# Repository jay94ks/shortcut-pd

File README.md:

# Simple Shortcut Keypad.
 This has six keys that are customizable, and this designed for disabled peoples. I'm working with disabled brother. he's a survivor of car-crash in highway, I don't know details. A few days ago, I asked him how to press `Ctrl + Alt + Del` key combinations, he answered that "I've gave up to press these kind of key combinations, forever". I thought that, if there is a special keyboard to help him, he will never need to give up to press complex key combinations. this project is for that.
 of course, this is also for gamers and quick `NSFW`, haha!

## Boards
This project is consisted of two boards. one is a USB hub port and `RP2040` board and other one is keypad board. this two boards are connected through `FPC` cable. and fixed by steel bolt bars.

### Lower board

### Upper board

### Assembly diagram

## Firmware
Work in progress

## Configuration Tool
Work in progress

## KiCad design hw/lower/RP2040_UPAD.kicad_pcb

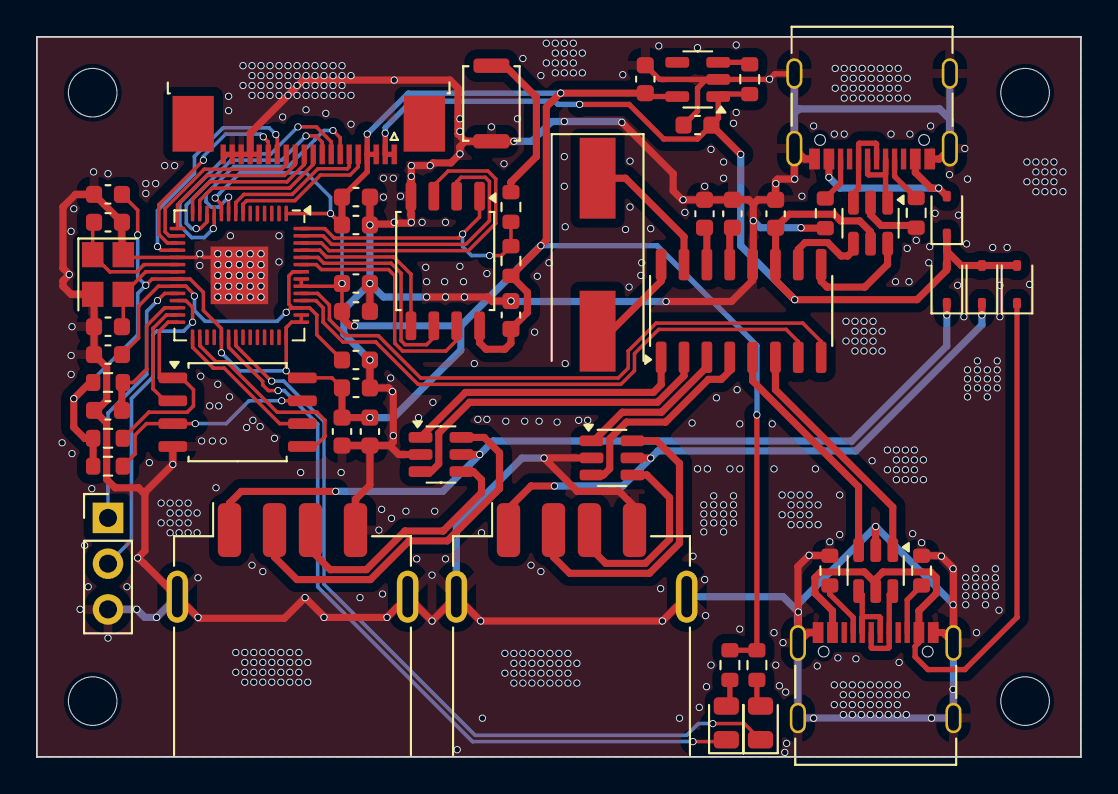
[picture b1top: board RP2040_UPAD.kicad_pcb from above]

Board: 2 copper layers, 58.0 x 40.0 mm, 59 parts (0 on the bottom side), 67 nets.

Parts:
C1, C8, C9, C10, C11, C13, C14, C15, C16: 100nF; C_0603_1608Metric
C2, C3: 30pF; C_0603_1608Metric
C5, C6, C7: 2.2uF; C_0603_1608Metric
C17, C18, C19, C20, C21: 10uF; C_0603_1608Metric
D1: LED/R; LED_0805_2012Metric
D2: LED/B; LED_0805_2012Metric
D3, D4, D6, D9: 1N5819WS; D_SOD-323
H1, H2, H3, H4: MountingHole; MountingHole_2.7mm_M2.5
J1: JTAG; PinHeader_1x03_P2.54mm_Vertical
J2, J5: USB_C_Receptacle_USB2.0; USB_C_Receptacle_Palconn_UTC16-G
J3, J4: USB_A; USB_A_Receptacle_GCT_USB1046
J6: 0.5mm FPC; TE_2-1734839-0_1x20-1MP_P0.5mm_Horizontal
R3: 100; R_0603_1608Metric
R4, R7, R10, R12: 10k; R_0603_1608Metric
R5, R6: 1k; R_0603_1608Metric
R11: 100k; R_0603_1608Metric
R13, R14, R18, R19: 5.1k; R_0603_1608Metric
SW1: SW_Push; SW_Push_SPST_NO_Alps_SKRK
U1: RP2040; QFN-56-1EP_7x7mm_P0.4mm_EP3.2x3.2mm
U2: W25Q128JVSS; SOIC-8_5.23x5.23mm_P1.27mm
U3: XC6220B331MR; SOT-23-5
U4: W25Q32JVSS; SOIC-8_5.23x5.23mm_P1.27mm
U5, U11, U12, U13: USBLC6-2SC6; SOT-23-6
U6: SL2.1A; SO-16_3.9x9.9mm_P1.27mm
Y1: 12MHz; Crystal_SMD_3225-4Pin_3.2x2.5mm
Y2: 12MHz; Crystal_SMD_HC49-SD

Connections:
+1V1: C5.2, C6.2, U1.23 (DVDD), U1.45 (VREG_VOUT), U1.50 (DVDD)
+3.3VD: C7.1, C8.1, C9.1, C10.1, C11.1, C13.1, C14.1, C15.1, C16.1, C18.1, J6.3, J6.4, R4.2, R5.2, R6.2, R7.1, R10.2, R12.1, U1.1 (IOVDD), U1.10 (IOVDD), U1.22 (IOVDD), U1.33 (IOVDD), U1.42 (IOVDD), U1.43 (ADC_AVDD), U1.44 (VREG_IN), U1.48 (USB_VDD), U1.49 (IOVDD), U2.8 (VCC), U3.5 (VOUT), U4.8 (VCC)
+5VD: C17.1, C21.1, D3.1 (K), D4.2 (A), D6.2 (A), D9.2 (A), J6.1, J6.2, R11.2, U3.1 (VIN), U5.5 (VBUS), U6.11 (VDD5)
/RP2040/QSPI_SCLK: U1.52 (QSPI_SCLK), U2.6 (CLK)
/RP2040/QSPI_SD0: U1.53 (QSPI_SD0), U2.5 (DI(IO0))
/RP2040/QSPI_SD1: U1.55 (QSPI_SD1), U2.2 (DO(IO1))
/RP2040/QSPI_SD2: U1.54 (QSPI_SD2), U2.3 (IO2)
/RP2040/QSPI_SD3: U1.51 (QSPI_SD3), U2.7 (IO3)
/RP2040/QSPI_SS: R3.1, R7.2, U1.56 (QSPI_SS), U2.1 (~CS)
/USB/USB_RAW_DM: J2.A7 (D-), J2.B7 (D-), U5.1 (I/O1)
/USB/USB_RAW_DP: J2.A6 (D+), J2.B6 (D+), U5.3 (I/O2)
GND: C1.2, C2.1, C3.1, C5.1, C6.1, C7.2, C8.2, C9.2, C10.2, C11.2, C13.2, C14.2, C15.2, C16.2, C17.2, C18.2, C19.1, C20.1, C21.2, J1.3, J2.A1 (GND), J2.A12 (GND), J2.B1 (GND), J2.B12 (GND), J2.S1 (SHIELD), J3.4 (GND), J3.5 (Shield), J4.4 (GND), J4.5 (Shield), J5.A1 (GND), J5.A12 (GND), J5.B1 (GND), J5.B12 (GND), J5.S1 (SHIELD), J6.16, J6.17, J6.18, J6.19, J6.20, R13.2, R14.1, R18.2, R19.1, SW1.1, U1.19 (TESTEN), U1.57 (GND), U2.4 (GND), U3.2 (GND), U4.4 (GND), U5.2 (GND), U6.12 (GND), U11.2 (GND), U12.2 (GND), U13.2 (GND), Y1.2, Y1.4
GP5/ROW1: J6.5, U1.7 (GPIO5)
GP6/ROW2: J6.6, U1.8 (GPIO6)
GP7/COL1: J6.7, U1.9 (GPIO7)
GP8/COL2: J6.8, U1.11 (GPIO8)
GP9/COL3: J6.9, U1.12 (GPIO9)
GP10/SPI1_SCK: J6.10, U1.13 (GPIO10)
GP11/SPI1_TX: J6.11, U1.14 (GPIO11)
GP12/SPI1_RX: J6.12, U1.15 (GPIO12)
GP13/SPI1_CSn: J6.13, U1.16 (GPIO13)
GP14/I2C1_SDA: J6.15, U1.17 (GPIO14)
GP15/I2C1_SCL: J6.14, U1.18 (GPIO15)
GP16/SPI0_RX: U1.27 (GPIO16), U4.2 (DO(IO1))
GP17/SPI0_CSn: R12.2, U1.28 (GPIO17), U4.1 (~CS)
GP18/SPI0_SCK: U1.29 (GPIO18), U4.6 (CLK)
GP19/SPI0_TX: U1.30 (GPIO19), U4.5 (DI(IO0))
GP22/LED_CR: D1.1 (K), U1.34 (GPIO22)
GP23/LED_CE: D2.1 (K), U1.35 (GPIO23)
unnamed: D1.2 (A), R5.1
unnamed: D2.2 (A), R6.1
unnamed: D4.1 (K), J5.A4 (VBUS), J5.A9 (VBUS), J5.B4 (VBUS), J5.B9 (VBUS), U13.5 (VBUS)
unnamed: D6.1 (K), J3.1 (VBUS), U11.5 (VBUS)
unnamed: D9.1 (K), J4.1 (VBUS), U12.5 (VBUS)
unnamed: J2.A5 (CC1), R13.1
unnamed: J2.B5 (CC2), R14.2
unnamed: J3.3 (D+), U11.4 (I/O2)
unnamed: J3.2 (D-), U11.6 (I/O1)
unnamed: J4.3 (D+), U12.4 (I/O2)
unnamed: J4.2 (D-), U12.6 (I/O1)
unnamed: J5.A5 (CC1), R18.1
unnamed: J5.B5 (CC2), R19.2
unnamed: J5.A6 (D+), J5.B6 (D+), U13.6 (I/O1)
unnamed: J5.A7 (D-), J5.B7 (D-), U13.4 (I/O2)
unnamed: R3.2, SW1.2
unnamed: C2.2, U1.20 (XIN), Y1.1
unnamed: C3.2, U1.21 (XOUT), Y1.3
unnamed: R11.1, U3.3 (CE)
unnamed: R10.1, U4.3 (IO2), U4.7 (IO3)
unnamed: C19.2, U6.14 (VDD18)
unnamed: C20.2, U6.13 (VDD33)
unnamed: U6.16 (XIN), Y2.2
unnamed: U6.15 (XOUT), Y2.1
RP2040_DM: U1.46 (USB_DM), U6.7 (DM1)
RP2040_DP: U1.47 (USB_DP), U6.8 (DP1)
RUN: C1.1, R4.1, U1.26 (RUN)
SWD_CLK: J1.1, U1.24 (SWCLK)
SWD_DIO: J1.2, U1.25 (SWD)
USBH1_DM: U6.3 (DM3), U11.1 (I/O1)
USBH1_DP: U6.4 (DP3), U11.3 (I/O2)
USBH2_DM: U6.1 (DM4), U12.1 (I/O1)
USBH2_DP: U6.2 (DP4), U12.3 (I/O2)
USBM2_DM: U6.5 (DM2), U13.3 (I/O2)
USBM2_DP: U6.6 (DP2), U13.1 (I/O1)
USB_DM: U5.6 (I/O1), U6.9 (DM)
USB_DP: U5.4 (I/O2), U6.10 (DP)
VBUS: D3.2 (A), J2.A4 (VBUS), J2.A9 (VBUS), J2.B4 (VBUS), J2.B9 (VBUS)

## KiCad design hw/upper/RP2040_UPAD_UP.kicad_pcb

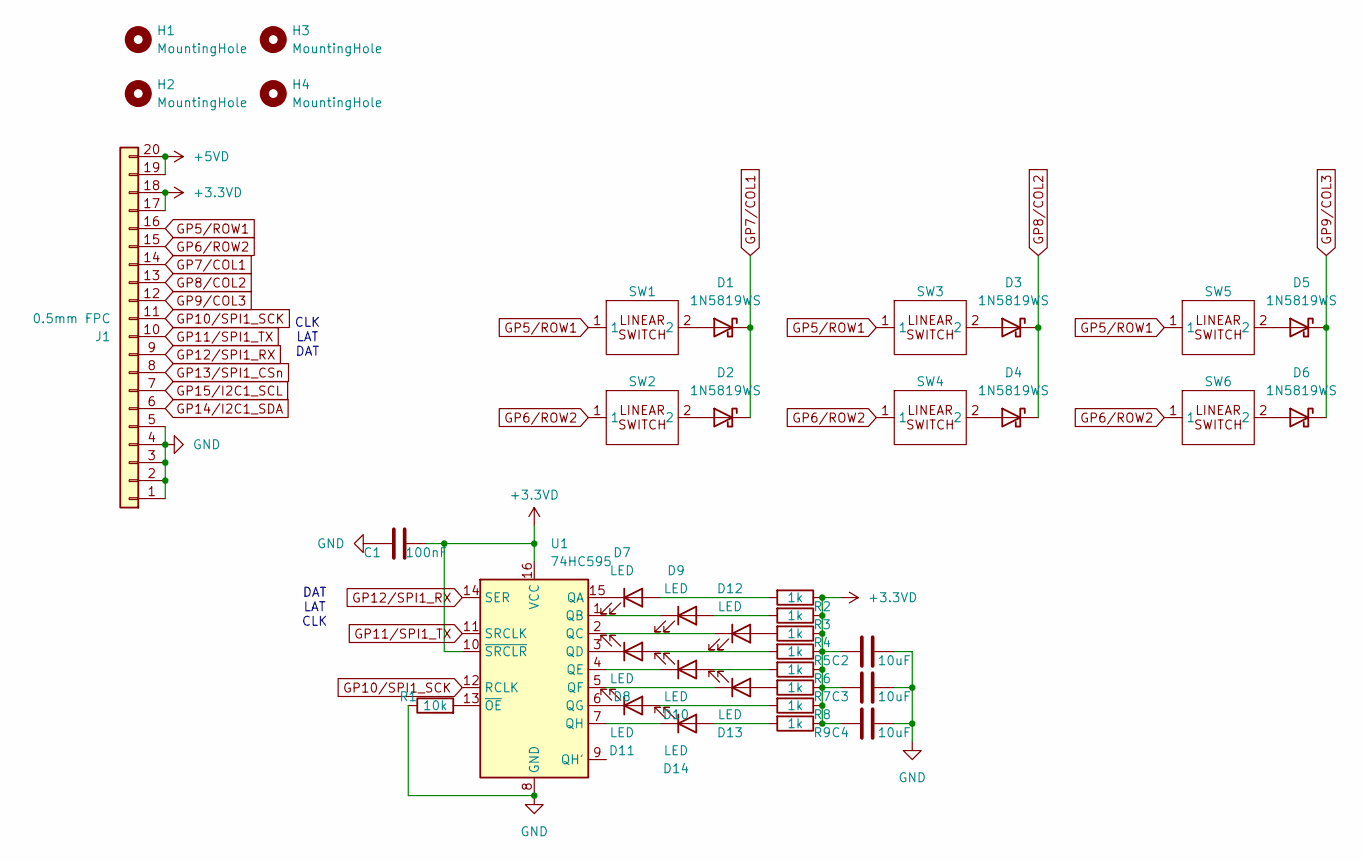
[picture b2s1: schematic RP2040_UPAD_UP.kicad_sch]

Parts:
C1: 100nF; C_0603_1608Metric
C2, C3, C4: 10uF; C_0603_1608Metric
D1, D2, D3, D4, D5, D6: 1N5819WS; D_SOD-323
D7, D8, D9, D10, D11, D12, D13, D14: LED; LED_0603_1608Metric
H1, H2, H3, H4: MountingHole; MountingHole_2.7mm_M2.5
J1: 0.5mm FPC; TE_2-1734839-0_1x20-1MP_P0.5mm_Horizontal
R1: 10k; R_0603_1608Metric
R2, R3, R4, R5, R6, R7, R8, R9: 1k; R_0603_1608Metric
SW1, SW2, SW3, SW4, SW5, SW6: Kailh_socket_MX_no_throughole
U1: 74HC595; SOP-16_4.55x10.3mm_P1.27mm

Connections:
+3.3VD: C1.2, C2.1, C3.1, C4.1, J1.17, J1.18, R2.1, R3.1, R4.1, R5.1, R6.1, R7.1, R8.1, R9.1, U1.10 (~SRCLR), U1.16 (VCC)
+5VD: J1.19, J1.20
GND: C1.1, C2.2, C3.2, C4.2, J1.1, J1.2, J1.3, J1.4, J1.5, R1.1, U1.8 (GND)
GP5/ROW1: J1.16, SW1.1, SW3.1, SW5.1
GP6/ROW2: J1.15, SW2.1, SW4.1, SW6.1
GP7/COL1: D1.1 (K), D2.1 (K), J1.14
GP8/COL2: D3.1 (K), D4.1 (K), J1.13
GP9/COL3: D5.1 (K), D6.1 (K), J1.12
GP10/SPI1_SCK: J1.11, U1.12 (RCLK)
GP11/SPI1_TX: J1.10, U1.11 (SRCLK)
GP12/SPI1_RX: J1.9, U1.14 (SER)
GP13/SPI1_CSn: J1.8
GP14/I2C1_SDA: J1.6
GP15/I2C1_SCL: J1.7
unnamed: D1.2 (A), SW1.2
unnamed: D2.2 (A), SW2.2
unnamed: D3.2 (A), SW3.2
unnamed: D4.2 (A), SW4.2
unnamed: D5.2 (A), SW5.2
unnamed: D6.2 (A), SW6.2
unnamed: D7.2 (A), R2.2
unnamed: D7.1 (K), U1.15 (QA)
unnamed: D8.2 (A), R5.2
unnamed: D8.1 (K), U1.3 (QD)
unnamed: D9.2 (A), R3.2
unnamed: D9.1 (K), U1.1 (QB)
unnamed: D10.2 (A), R6.2
unnamed: D10.1 (K), U1.4 (QE)
unnamed: D11.2 (A), R8.2
unnamed: D11.1 (K), U1.6 (QG)
unnamed: D12.2 (A), R4.2
unnamed: D12.1 (K), U1.2 (QC)
unnamed: D13.2 (A), R7.2
unnamed: D13.1 (K), U1.5 (QF)
unnamed: D14.2 (A), R9.2
unnamed: D14.1 (K), U1.7 (QH)
unnamed: R1.2, U1.13 (~OE)

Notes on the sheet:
CLK LAT DAT
DAT LAT CLK

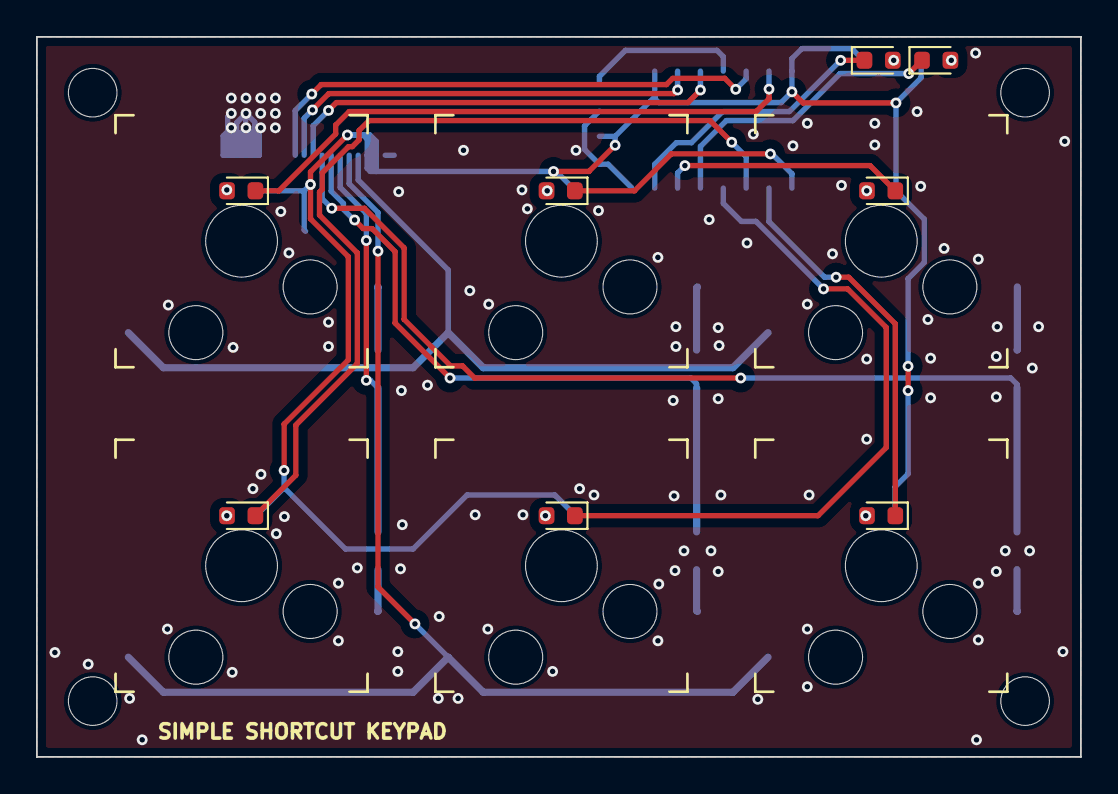
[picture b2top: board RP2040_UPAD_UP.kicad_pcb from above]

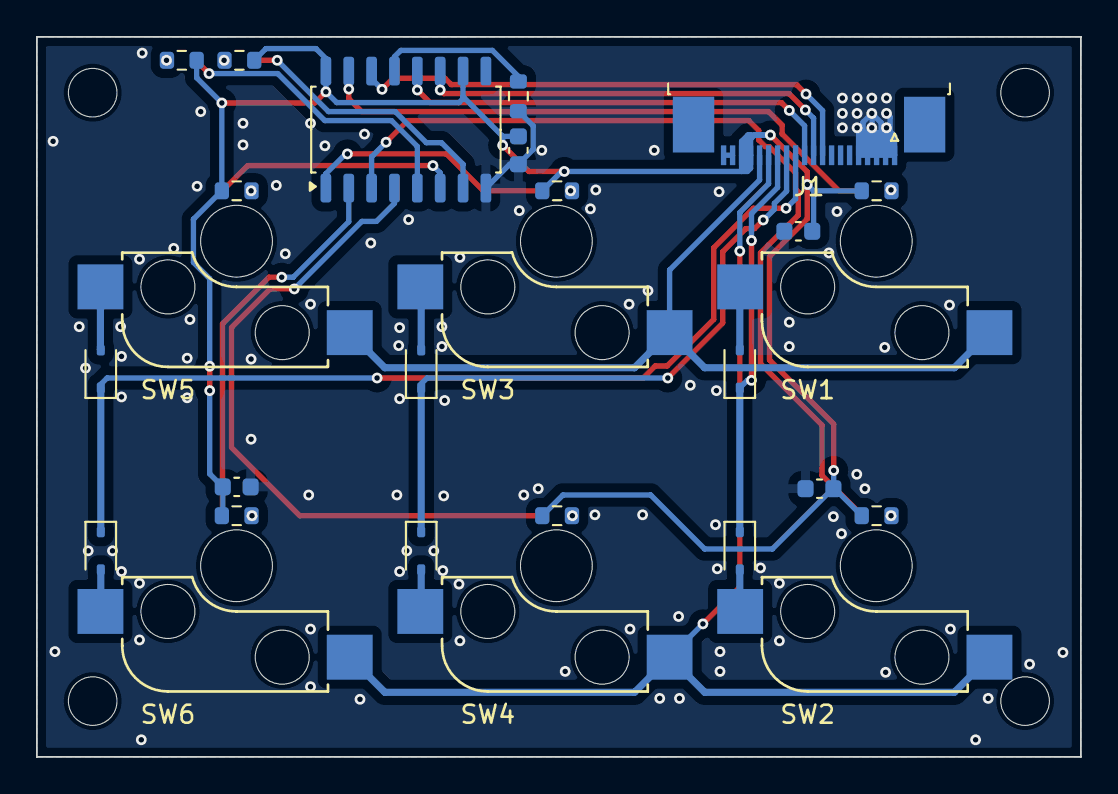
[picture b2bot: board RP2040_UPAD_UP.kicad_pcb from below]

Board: 2 copper layers, 58.0 x 40.0 mm, 39 parts (21 on the bottom side), 34 nets.

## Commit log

2024-06-14 Firmware
